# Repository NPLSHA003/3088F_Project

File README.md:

# Dual Sensing Sensation

Introduction

This project is a light and temperature sensing project that detects light and the temperature as an external environmental stimulus. The sensors are built on to a board with its own power supply that will be able to power the microcontroller and the sensors. The board with the sensors on is called the HAT and will be able to fit on the microcontroller. The temperature sensor is an analohg sensor with a built in ADC that detects the exact temperature where as the light sensor is digital and is just used to detect whether there is or is not any light. Both sensors send the data to an EEPROM which is then reaad by a microcontroller. This project can be used for many applications such as monitoring light and temperature on a farm, for security purposes in checking for any immediate change in temperature and light in a room and many more.

What you will need for this project

Hardware:
Microcontroller - STM32Discovery board (The exact one we used was from the University of Cape Town
HAT - The  Dual sensing sensation board
Some Male pin headers
3.7 V Li-ion Battery Cell
USB micro B charger
USB mini B to USB micro B cable

Software:
Kicad or Altium 
stmCubic

Tools:
Soldering Iron and some solder
Multimeter

Notes:
Microcontroller: The exact microcontroller we used was from the University of Cape Town. You should perhaps get in contact with Justin Pead from the engineering department at UCT to get the exact one making the project easier to implement.
To get the Dual Sensing sensation board you will have to order it from JLPCB using the provided Gerber, BOM(Bill of materials) and CPL(Position) files. 
You could use Kicad or Altium to change certain internal circuits on the dual sensing sensation board. Take note that you would then need to change the PCB files and get the correct gerber, BOM and CPL files.

Connecting and testing the Hardware

Connecting:
Solder male pin headers to the individual test point. Proceed to the testing before connecting the dual sensing sensation board to the microcontroller.
You can then refer to the schematic to see which pins from the DSS board connect to which pins on the microcontroller.
After this fisrt connect the microcontroller board to a laptop. 
Run stmCubic.
It should pick up the board. You can then refer to the cody reference, copy and paste the functions and run it.
You can now connect power supply of the board to the microcontroller. It will save the temperature and light data and you can just connect your laptop/pc to the microcontroller to access this data.  

Testing:
1. Using the multimeter, measure the voltage across the battery. It should be between 2.2 V and 3.7 V.
2. Insert the battery in the battery holder on the board. Measure the voltage across TP6(positive terminal) and TP5(ground terminal). If the voltage across this is O V(or anywhere below 1 V) you have inserted the battery incorrectly. Fix it and measure the voltage again just to be sure.
3. Then measure the voltage between TP11 and TP5 this should be 3.3 V or very close to it.
4. You can then insert a micro B usb charger at the charger. To check if the battery is charging measure the current between TP7 and the positive terminal of the battery it should be 1 A.
5. You can now head over back to connecting.

Licencing 

This project uses a CC BY-SA liscence. You can use this project as would like as long as you credit us and more importantly share and commit any changes/adaptations/innovations to the project.

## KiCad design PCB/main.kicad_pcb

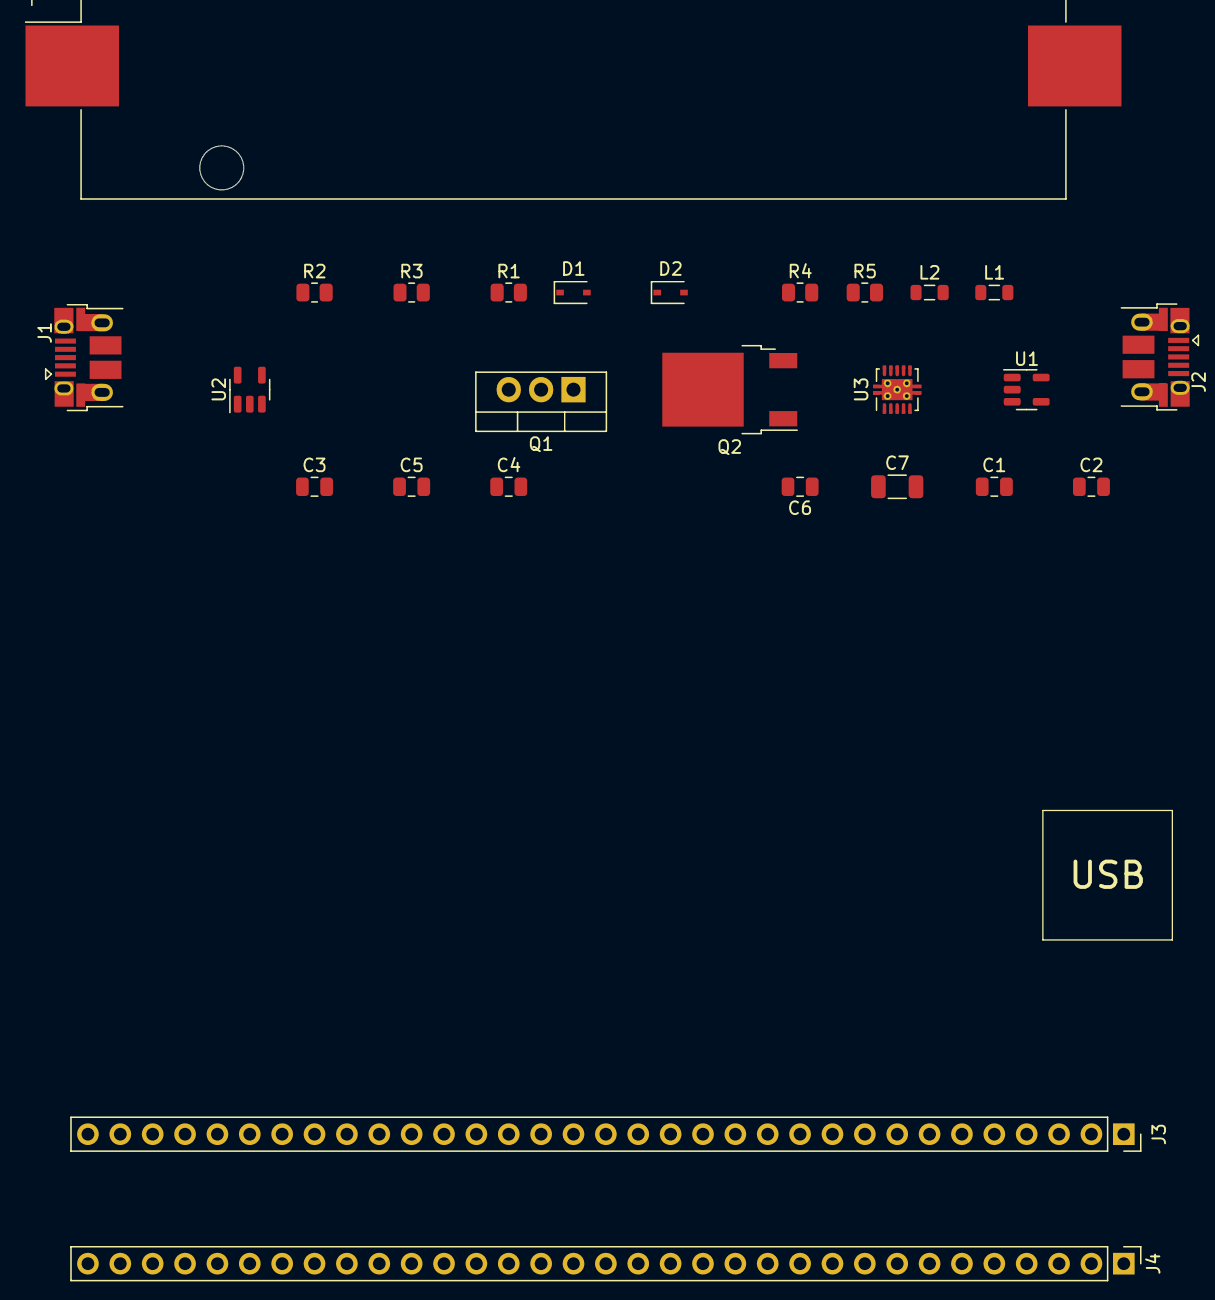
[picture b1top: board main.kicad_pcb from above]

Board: 2 copper layers, 26 parts (0 on the bottom side), 48 nets, no tracks yet.

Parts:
BT1: 3.7 V; BatteryHolder_Keystone_1042_1x18650
C1, C2, C3, C4, C5: 4.7 uF; C_0805_2012Metric
C6: 1uF; C_0805_2012Metric
C7: 22 uF; C_1206_3216Metric
D1: BAT60A; D_SOD-323
D2: D_Schottky; D_SOD-323
J1, J2: USB_B_Micro; USB_Micro-B_Amphenol_10103594-0001LF_Horizontal
J3: Conn_01x33_Female; PinSocket_1x33_P2.54mm_Vertical
J4: Conn_01x33_Female; PinHeader_1x33_P2.54mm_Vertical
L1, L2: 2.2 uH; L_0805_2012Metric
Q1: FQP27P06; TO-220-3_Vertical
Q2: Q_PMOS_DSG; TO-252-2
R1: 100k; R_0805_2012Metric
R2, R3: 10k; R_0805_2012Metric
R4: 2M; R_0805_2012Metric
R5: 180K; R_0805_2012Metric
U1: LM3670MF; TSOT-23-5
U2: MCP73831-2-OT; SOT-23-5
U3: TPS61200DRC; Texas_S-PVSON-N10_ThermalVias

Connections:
+5V: J3.1, J4.1
/BOOT: J3.6, J4.6
/Microcontroller: C2.1, J2.1 (VBUS), L1.2, U1.4 (FB)
/PA8: J3.25, J4.25
/PA9: J3.24, J4.24
/PA10: J3.23, J4.23
/PA11: J3.22, J4.22
/PA12: J3.21, J4.21
/PA13: J3.20, J4.20
/PA14: J3.17, J4.17
/PA15: J3.16, J4.16
/PB3: J3.11, J4.11
/PB4: J3.10, J4.10
/PB5: J3.9, J4.9
/PB6: J3.8, J4.8
/PB7: J3.7, J4.7
/PB8: J3.4, J4.4
/PB9: J3.3, J4.3
/PB13: J3.32, J4.32
/PB14: J3.31, J4.31
/PB15: J3.30, J4.30
/PC6: J3.29, J4.29
/PC7: J3.28, J4.28
/PC8: J3.27, J4.27
/PC9: J3.26, J4.26
/PC10: J3.15, J4.15
/PC11: J3.14, J4.14
/PC12: J3.13, J4.13
/PD2: J3.12, J4.12
/PF6: J3.19, J4.19
/PF7: J3.18, J4.18
/UVLO: C1.1, U1.1 (Vin)
Buck convertor: C7.1, D2.1 (K), U3.2 (VOUT), U3.10 (FB)
GND: BT1.2 (-), C1.2, C2.2, C4.2, C5.2, C6.2, C7.2, J1.4 (ID), J1.5 (GND), J1.6 (Shield), J2.4 (ID), J2.5 (GND), J2.6 (Shield), J3.2, J3.33, J4.2, J4.33, R3.2, R5.2, U1.2 (GND), U2.2 (VSS), U3.4 (PGND), U3.9 (GND), U3.11 (PAD)
unnamed: C3.2, R2.2
unnamed: C4.1, L2.1, Q2.1 (D), R4.1, U3.5 (VIN), U3.6 (EN), U3.8 (PS)
unnamed: C6.1, U3.1 (VAUX)
unnamed: D1.2 (A), Q1.1 (G), R1.1
unnamed: J1.2 (D-), J1.3 (D+)
unnamed: J2.2 (D-), J2.3 (D+)
unnamed: L1.1, U1.5 (SW)
unnamed: L2.2, U3.3 (L)
unnamed: R2.1, U2.5 (PROG)
unnamed: R4.2, R5.1, U3.7 (UVLO)
Pin 2: D1.1 (K), Q1.3 (S), Q2.2 (S)
Pin 3: C3.1, D2.2 (A), J1.1 (VBUS), Q2.3 (G), R3.1, U2.4 (VDD)
Reverse Polarity protecion: BT1.1 (+), C5.1, U2.3 (VBAT)
VDD: J3.5, J4.5

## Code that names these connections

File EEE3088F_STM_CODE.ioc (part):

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Mcu.Name=STM32F051R8Tx
Mcu.Package=LQFP64
Mcu.UserName=STM32F051R8Tx
PA0.GPIOParameters=GPIO_Label,GPIO_ModeDefaultEXTI
PA0.GPIO_Label=B1 [Blue PushButton]
PA0.GPIO_ModeDefaultEXTI=GPIO_MODE_EVT_RISING
PA0.Signal=GPXTI0
PA13.GPIOParameters=GPIO_Label
PA13.GPIO_Label=SWDIO
PA13.Mode=Serial_Wire
PA13.Signal=SYS_SWDIO
PA14.GPIOParameters=GPIO_Label
PA14.GPIO_Label=SWCLK
PA14.Mode=Serial_Wire
PA14.Signal=SYS_SWCLK
PB8.Mode=I2C
PB8.Signal=I2C1_SCL
PB9.Mode=I2C
PB9.Signal=I2C1_SDA
PC8.GPIOParameters=GPIO_Label
PC8.GPIO_Label=LD4 [Blue Led]
PC8.Signal=GPIO_Output
PC9.GPIOParameters=GPIO_Label
PC9.GPIO_Label=LD3 [Green Led]
PC9.Signal=GPIO_Output
RCC.SYSCLKFreq_VALUE=48000000
RCC.SYSCLKSource=RCC_SYSCLKSOURCE_PLLCLK
board=STM32F0DISCOVERY
boardIOC=true

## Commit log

2022-03-04 Uploaded draft BOM for power
2022-03-04 Add files via upload
    The Bill of Material for Sensor P1
2022-03-07 picture uploaded
2022-03-11 removed draft BOM
2022-03-11 Uploaded latest BOM
2022-03-11 BOM FOR SENSORS.V1
    This is the initial design bill of material
2022-03-11 Sensor v1
    Schematic for initial design
2022-03-20 Updated BOM
    Includes total budget
2022-05-21 Draft readme
    Let other group members read it and then commit any final changes
2022-05-23 attmpted code
2022-05-23 attempted code
2022-05-23 project description
2022-05-23 Create SRC
2022-05-23 Create txt
2022-05-23 STM functions
2022-05-23 added code ref
2022-05-23 Contribution How To Guide.md
    Contributing to Dual Sensor Sensation(Group 24):
    Designers for the HAT:
    Tlokomelo Nlosi:NKSREG002@myuct.ac.za
    Kabelo Manake:MNKKAB001@myuct.ac.za
    Shane Napoleon:NPLSHA003@myuct.ac.za
    Contributions to this project are welcome, however, the guide below must be read and adhered to
